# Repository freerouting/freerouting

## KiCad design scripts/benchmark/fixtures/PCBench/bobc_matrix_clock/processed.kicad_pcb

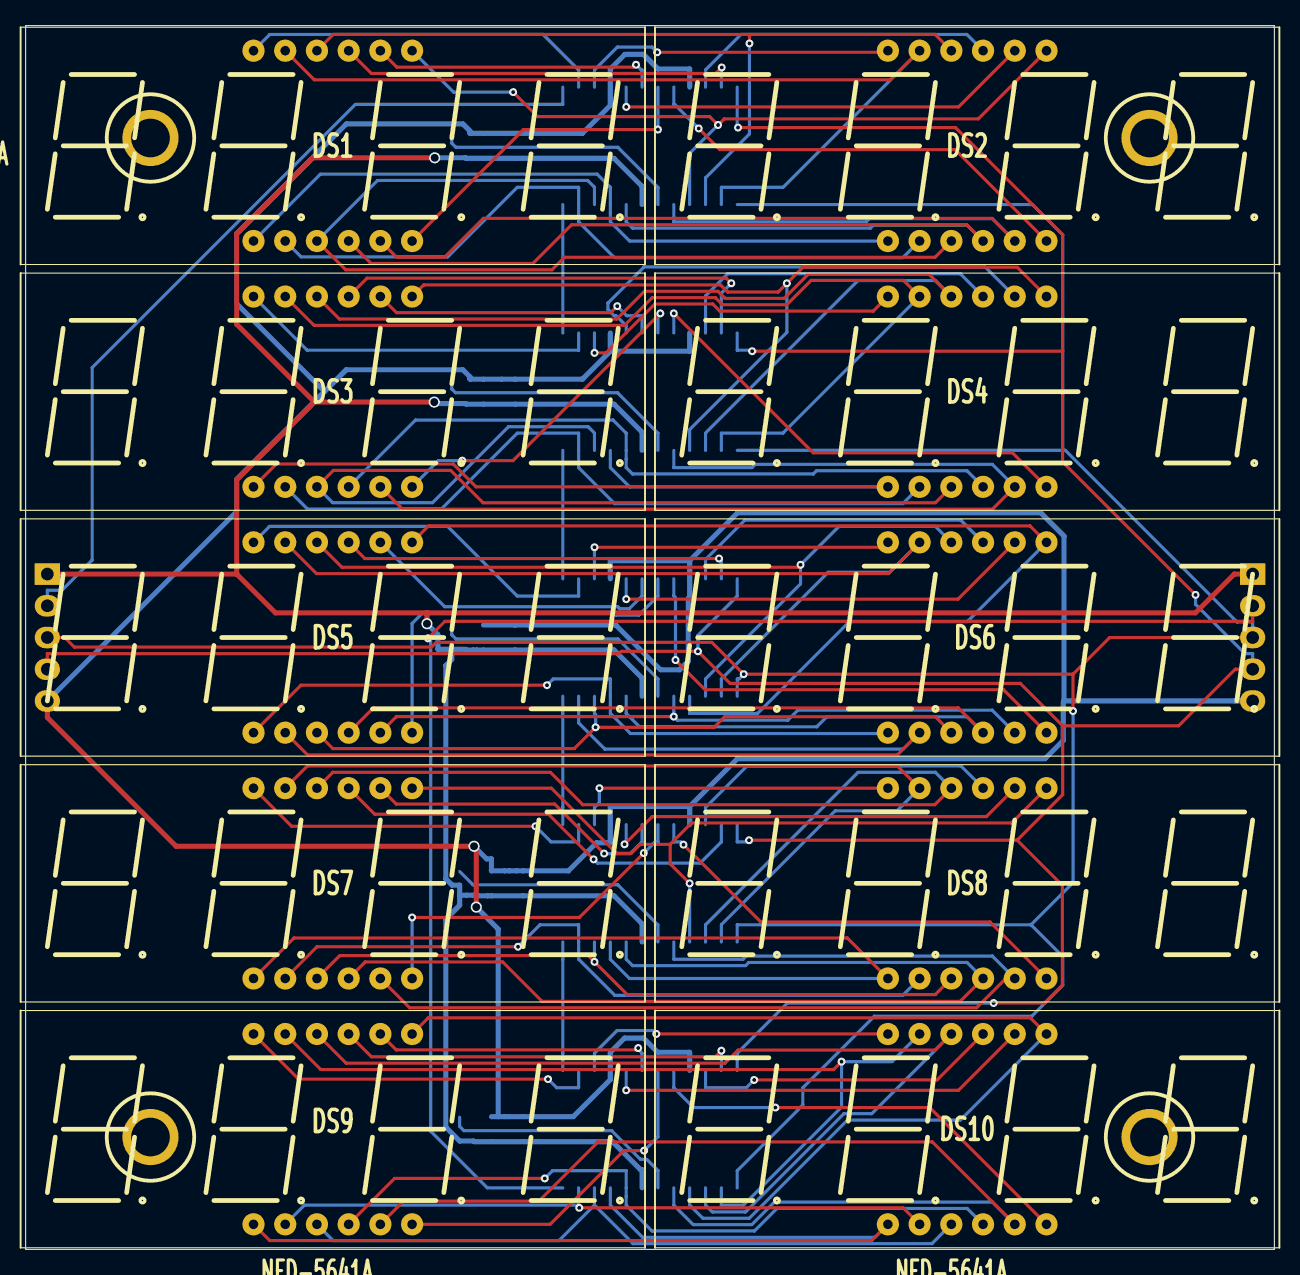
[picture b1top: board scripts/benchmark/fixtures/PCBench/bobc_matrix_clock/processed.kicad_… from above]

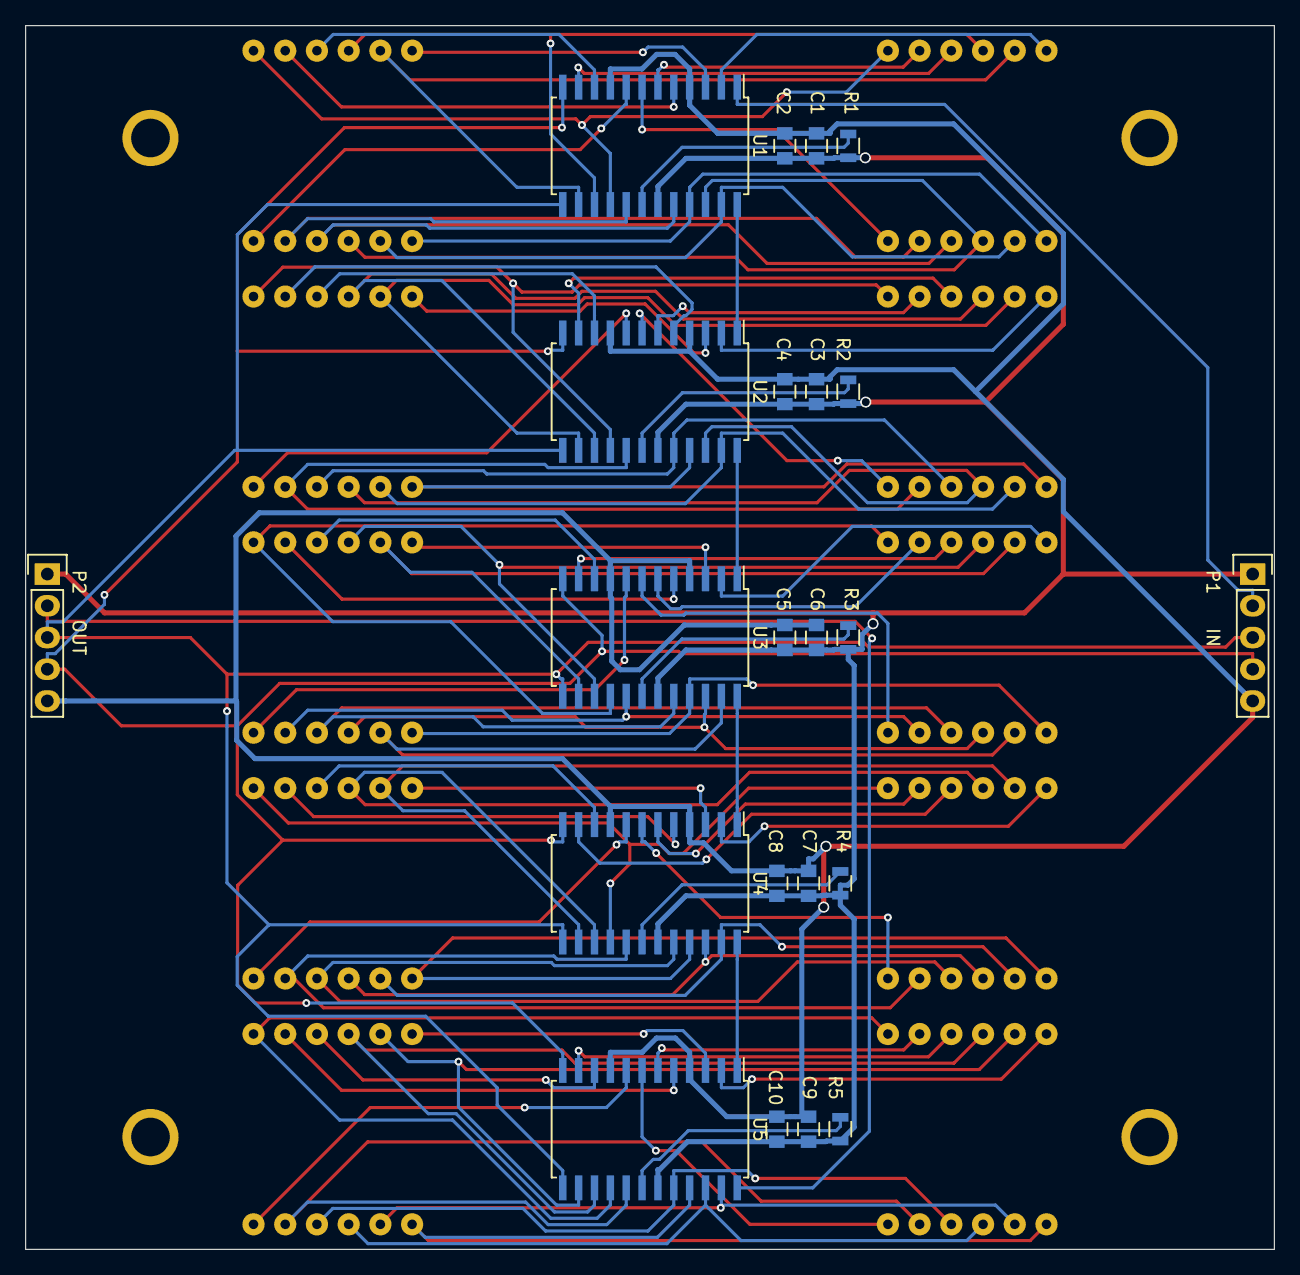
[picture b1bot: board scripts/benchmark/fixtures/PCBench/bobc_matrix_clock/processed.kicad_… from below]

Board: 2 copper layers, 100.0 x 98.0 mm, 36 parts (22 on the bottom side), 95 nets.

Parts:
C1, C3, C5, C7, C9: 10uF; C_0805
C2, C4, C6, C8, C10: 100nF; C_0805
DS1, DS2, DS3, DS4, DS5, DS6, DS7, DS8, DS9, DS10: NFD-5641A; NFD-5641
H1, H2, H3, H4: HOLE_RMC; HOLE_M3
P1: IN; Socket_Strip_Straight_1x05
P2: OUT; Socket_Strip_Straight_1x05
R1, R2, R3, R4, R5: 28k; R_0805
U1, U2, U3, U4, U5: MAX7219; SOIC-24_7.5x15.4mm_Pitch1.27mm

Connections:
/Digits Row 1/CLK: P1.3, P2.3, U1.13, U2.13, U3.13, U4.13, U5.13
/Digits Row 1/DIN: P1.2, U1.1
/Digits Row 1/LOAD: P1.4, P2.4, U1.12, U2.12, U3.12, U4.12, U5.12
/Digits Row 1/SEG_A: DS1.11, DS2.11, U1.14
/Digits Row 1/SEG_B: DS1.7, DS2.7, U1.16
/Digits Row 1/SEG_C: DS1.4, DS2.4, U1.20
/Digits Row 1/SEG_D: DS1.2, DS2.2, U1.23
/Digits Row 1/SEG_DP: DS1.3, DS2.3, U1.22
/Digits Row 1/SEG_E: DS1.1, DS2.1, U1.21
/Digits Row 1/SEG_F: DS1.10, DS2.10, U1.15
/Digits Row 1/SEG_G: DS1.5, DS2.5, U1.17
/Row 2/DIN: U1.24, U2.1
/Row 2/SEG_A: DS3.11, DS4.11, U2.14
/Row 2/SEG_B: DS3.7, DS4.7, U2.16
/Row 2/SEG_C: DS3.4, DS4.4, U2.20
/Row 2/SEG_D: DS3.2, DS4.2, U2.23
/Row 2/SEG_DP: DS3.3, DS4.3, U2.22
/Row 2/SEG_E: DS3.1, DS4.1, U2.21
/Row 2/SEG_F: DS3.10, DS4.10, U2.15
/Row 2/SEG_G: DS3.5, DS4.5, U2.17
/Row 3/DIN: U2.24, U3.1
/Row 3/SEG_A: DS5.11, DS6.11, U3.14
/Row 3/SEG_B: DS5.7, DS6.7, U3.16
/Row 3/SEG_C: DS5.4, DS6.4, U3.20
/Row 3/SEG_D: DS5.2, DS6.2, U3.23
/Row 3/SEG_DP: DS5.3, DS6.3, U3.22
/Row 3/SEG_E: DS5.1, DS6.1, U3.21
/Row 3/SEG_F: DS5.10, DS6.10, U3.15
/Row 3/SEG_G: DS5.5, DS6.5, U3.17
/Row 4/DIN: U3.24, U4.1
/Row 4/SEG_A: DS7.11, DS8.11, U4.14
/Row 4/SEG_B: DS7.7, DS8.7, U4.16
/Row 4/SEG_C: DS7.4, DS8.4, U4.20
/Row 4/SEG_D: DS7.2, DS8.2, U4.23
/Row 4/SEG_DP: DS7.3, DS8.3, U4.22
/Row 4/SEG_E: DS7.1, DS8.1, U4.21
/Row 4/SEG_F: DS7.10, DS8.10, U4.15
/Row 4/SEG_G: DS7.5, DS8.5, U4.17
/Row 5/DIN: U4.24, U5.1
/Row 5/DOUT: P2.2, U5.24
/Row 5/SEG_A: DS9.11, DS10.11, U5.14
/Row 5/SEG_B: DS9.7, DS10.7, U5.16
/Row 5/SEG_C: DS9.4, DS10.4, U5.20
/Row 5/SEG_D: DS9.2, DS10.2, U5.23
/Row 5/SEG_DP: DS9.3, DS10.3, U5.22
/Row 5/SEG_E: DS9.1, DS10.1, U5.21
/Row 5/SEG_F: DS9.10, DS10.10, U5.15
/Row 5/SEG_G: DS9.5, DS10.5, U5.17
GND: C1.2, C2.2, C3.2, C4.2, C5.2, C6.2, C7.2, C8.2, C9.2, C10.2, P1.5, P2.5, U1.4, U1.9, U2.4, U2.9, U3.4, U3.9, U4.4, U4.9, U5.4, U5.9
unnamed: DS1.6, U1.7
unnamed: DS1.8, U1.6
unnamed: DS1.9, U1.11
unnamed: DS1.12, U1.2
unnamed: DS2.6, U1.8
unnamed: DS2.8, U1.5
unnamed: DS2.9, U1.10
unnamed: DS2.12, U1.3
unnamed: DS3.6, U2.7
unnamed: DS3.8, U2.6
unnamed: DS3.9, U2.11
unnamed: DS3.12, U2.2
unnamed: DS4.6, U2.8
unnamed: DS4.8, U2.5
unnamed: DS4.9, U2.10
unnamed: DS4.12, U2.3
unnamed: DS5.6, U3.7
unnamed: DS5.8, U3.6
unnamed: DS5.9, U3.11
unnamed: DS5.12, U3.2
unnamed: DS6.6, U3.8
unnamed: DS6.8, U3.5
unnamed: DS6.9, U3.10
unnamed: DS6.12, U3.3
unnamed: DS7.6, U4.7
unnamed: DS7.8, U4.6
unnamed: DS7.9, U4.11
unnamed: DS7.12, U4.2
unnamed: DS8.6, U4.8
unnamed: DS8.8, U4.5
unnamed: DS8.9, U4.10
unnamed: DS8.12, U4.3
unnamed: DS9.6, U5.7
unnamed: DS9.8, U5.6
unnamed: DS9.9, U5.11
unnamed: DS9.12, U5.2
unnamed: DS10.6, U5.8
unnamed: DS10.8, U5.5
unnamed: DS10.9, U5.10
unnamed: DS10.12, U5.3
unnamed: R1.2, U1.18
unnamed: R2.2, U2.18
unnamed: R3.2, U3.18
unnamed: R4.2, U4.18
unnamed: R5.2, U5.18
VCC: C1.1, C2.1, C3.1, C4.1, C5.1, C6.1, C7.1, C8.1, C9.1, C10.1, P1.1, P2.1, R1.1, R2.1, R3.1, R4.1, R5.1, U1.19, U2.19, U3.19, U4.19, U5.19

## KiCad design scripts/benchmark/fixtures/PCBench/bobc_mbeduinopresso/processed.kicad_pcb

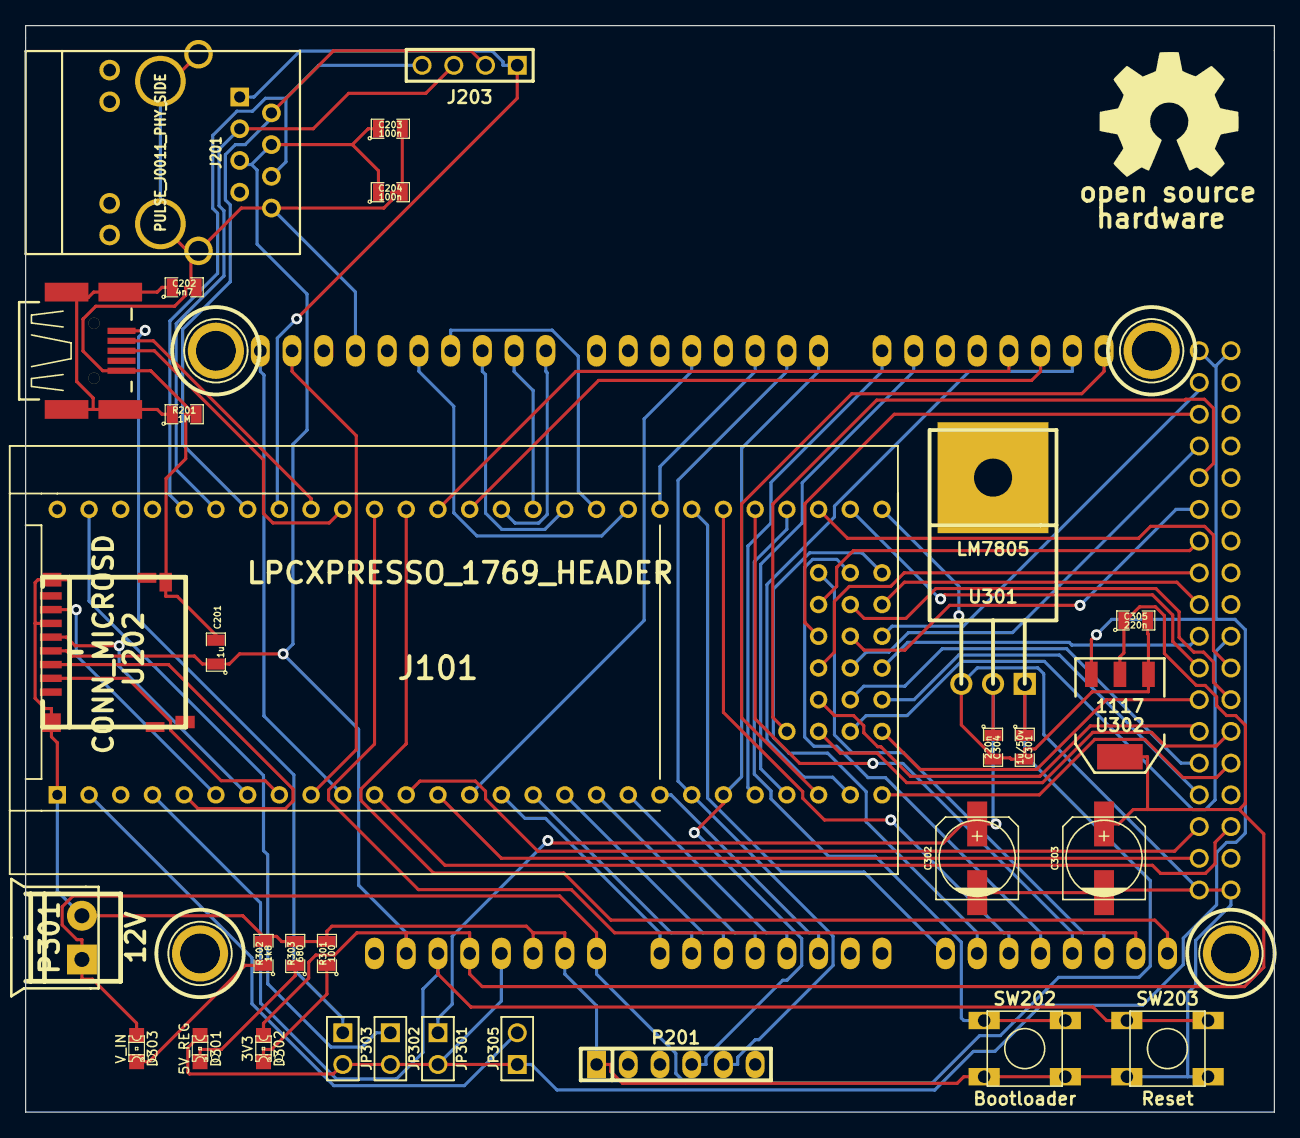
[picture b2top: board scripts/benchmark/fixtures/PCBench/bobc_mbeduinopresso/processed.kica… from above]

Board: 2 copper layers, 100.0 x 87.0 mm, 37 parts (0 on the bottom side), 77 nets.

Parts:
C201: 1u; SM0805
C202: 4n7; SM0805
C203, C204: 100n; SM0805
C301: 1u/50v; SM0805
C302, C303: 100u; c_elec_6.3x5.7
C304, C305: 220n; SM0805
D301: 5V_REG; LED-0805_GREEN
D302: 3V3; LED-0805_GREEN
D303: V_IN; LED-0805_GREEN
H201, H202, H203, H204: HOLE_RMC; HOLE_M3
J101: LPCXPRESSO_1769_HEADER; MBED_LPCXPRESSO
J201: PULSE_J0011_PHY_SIDE; RJ45_Halo_HFJ11
J203: Enet; PIN_ARRAY_4x1
JP301, JP302, JP303, JP305: JUMPER; PIN_ARRAY_2X1
M201: LOGO_OSHW; OSHW_logo_2
P201: SERIAL; pin_strip_6
P301: 12V; RMC-pt_1,5-2-3,5-h
R201: 1M; SM0805
R301: 100; SM0805
R302: 1k8; SM0805
R303: 680; SM0805
SHIELD101: ARDUINO_DUE_SHIELD; ARDUINO_MEGA_DUE_SHIELD_FOOTPRINT_RMC
SW202: Bootloader; SW_6x6_MULTI
SW203: Reset; SW_6x6_MULTI
U201: USBCONN; CONN_MiniAB_SMT_RMC
U202: CONN_MICROSD; MICRO_SD_DM3D
U301: LM7805; TO220
U302: 1117; SOT223

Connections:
*Bootloader: J101.51, SW202.1
*ETH_RD+: J101.33, J201.3, J203.3
*ETH_RD-: J101.32, J201.6, J203.4
*ETH_TD+: J101.35, J201.1, J203.1
*ETH_TD-: J101.34, J201.2, J203.2
*RESET: J101.4, SHIELD101.RST, SW203.1
*RX: J101.22, P201.4, SHIELD101.0
*TX: J101.21, P201.5, SHIELD101.1
*USB-D+: J101.37, U201.3
*USB-D-: J101.36, U201.2
+3.3V: C201.1, C203.1, C204.1, C303.1, C305.1, D302.1, J201.4, J201.5, SHIELD101.3V3, SHIELD101.IORF, U202.4, U302.2, U302.4
+5V: D301.1, JP301.2, JP302.2, JP303.2, JP305.1, SHIELD101.5V, SHIELD101.5V_4, SHIELD101.5V_5, U302.3
/Power/5V_REG: C302.1, C304.1, JP301.1, U301.3
AD4: J101.19, SHIELD101.AD4
AD5: J101.20, SHIELD101.AD5
CS_1: J101.8, U202.2
E0-DIR: J101.119, SHIELD101.28
E0-EN: J101.116, SHIELD101.42
E0-STEP: J101.104, SHIELD101.36
E1-DIR: J101.52, SHIELD101.41
E1-EN: J101.117, SHIELD101.39
E1-STEP: J101.105, SHIELD101.43
E2-DIR: J101.27, SHIELD101.47
E2-EN: J101.118, SHIELD101.45
E2-STEP: J101.106, SHIELD101.32
ESTOP: J101.53, SHIELD101.40
GND: C201.2, C202.2, C203.2, C204.2, C301.2, C302.2, C303.2, C304.2, C305.2, J101.1, J101.54, J201.8, J201.13, P201.1, P301.2, R201.2, R301.2, R302.2, R303.2, SHIELD101.GND, SW202.2, SW203.2, U201.4, U202.6, U202.9, U202.11, U301.2, U302.1
LPC_VIN: J101.2, JP305.2
MISO_0: J101.12, SHIELD101.50
MISO_1: J101.6, U202.7
MOSI_0: J101.11, SHIELD101.51
MOSI_1: J101.5, U202.3
unnamed: C202.1, R201.1, U201.5
unnamed: D301.2, R303.1
unnamed: D302.2, R301.1
unnamed: D303.2, R302.1
P0.4: J101.38, SHIELD101.AD14
P0.5: J101.39, SHIELD101.AD15
P0.21: J101.23, SHIELD101.14
P0.22: J101.24, SHIELD101.15
POWER1: J101.42, SHIELD101.8
POWER2: J101.43, SHIELD101.9
POWER3: J101.44, SHIELD101.10
POWER4: J101.45, SHIELD101.11
POWER5: J101.46, SHIELD101.12
POWER6: J101.47, SHIELD101.2
RXD2_SCL2: J101.41, SHIELD101.19
RXD3_SCL1: J101.10, SHIELD101.SCL1
SCK_0: J101.13, SHIELD101.52
SCK_1: J101.7, U202.5
SCL0: J101.26, SHIELD101.20
SDA0: J101.25, SHIELD101.21
SSEL_0: J101.14, SHIELD101.4
THERM0: J101.15, SHIELD101.AD0
THERM1: J101.16, SHIELD101.AD1
THERM2: J101.17, SHIELD101.AD2
THERM3: J101.18, SHIELD101.AD3
TXD2_SDA2: J101.40, SHIELD101.18
TXD3_SDA1: J101.9, SHIELD101.SDA1
VIN: C301.1, D303.1, P301.1, SHIELD101.V_IN, U301.1
VUSB1: J101.29, JP302.1
VUSB2: JP303.1, U201.1
X-DIR: J101.48, SHIELD101.AD8
X-EN: J101.113, SHIELD101.48
X-STEP: J101.101, SHIELD101.AD9
XMAX: J101.108, SHIELD101.30
XMIN: J101.107, SHIELD101.22
Y-DIR: J101.49, SHIELD101.AD10
Y-EN: J101.114, SHIELD101.46
Y-STEP: J101.102, SHIELD101.AD11
YMAX: J101.110, SHIELD101.38
YMIN: J101.109, SHIELD101.24
Z-DIR: J101.50, SHIELD101.AD12
Z-EN: J101.115, SHIELD101.44
Z-STEP: J101.103, SHIELD101.AD13
ZMAX: J101.112, SHIELD101.34
ZMIN: J101.111, SHIELD101.26

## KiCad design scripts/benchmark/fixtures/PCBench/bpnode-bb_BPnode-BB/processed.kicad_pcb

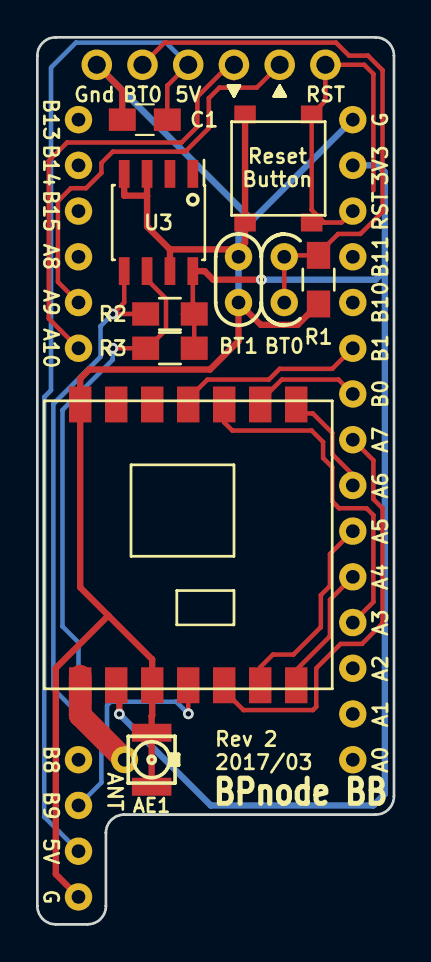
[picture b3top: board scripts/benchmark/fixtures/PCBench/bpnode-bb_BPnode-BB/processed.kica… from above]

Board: 2 copper layers, 19.8 x 49.3 mm, 10 parts (0 on the bottom side), 18 nets.

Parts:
AE1: Antenna_Shield; U.FL-COAX
C1: 0.1u; C_0805_HandSoldering
P1: CONN_01X06; Pin_Header_Angled_1x06_Pitch2.54mm
R1, R2, R3: R; R_0805_HandSoldering
SW1: SW_Push; SMD_BUTTON
U1: BP; BLUEPILL-EXTENSION
U2: RFM69; RFM69CW
U3: M24M02-DR; SOIC-8_3.9x4.9mm_Pitch1.27mm

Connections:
+3V3: R2.2, R3.2, U1.3V3, U2.2, U3.8
DIO0: U1.PB0, U2.9
DIO1: U1.PB1, U2.11
DIO2: U1.PA3, U2.10
DIO3: U1.PB9, U2.4
DTR: P1.6, SW1.1, U1.NRST
GND: AE1.2, C1.2, P1.1, R1.1, SW1.2, U1.G, U1.PB2, U2.3, U2.14, U3.3, U3.4, U3.7
MISO: U1.PA6, U2.8
MOSI: U1.PA7, U2.5
unnamed: AE1.1, U2.1
RTS: P1.2, R1.2, U1.BOOT
RX: P1.5, U1.PA9
SCL: R3.1, U1.PB6, U3.6
SCLK: U1.PA5, U2.6
SDA: R2.1, U1.PB7, U3.5
SSEL: U1.PA4, U2.7
TX: P1.4, U1.PA10
Vin: C1.1, P1.3, U1.5V
